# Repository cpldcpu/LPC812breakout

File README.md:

LPC812breakout
==============

Breakout Board for the NXP LPC812M101JPH20 microcontroller. Includes push buttons for reset and activating the serial bootloader. 
The board has an integrated 500mA 3.3V LDO to supply both the MCU and connected devices from the USB port. 

The four pins on the top side (5V,RX,TX,GND) can be used to connect a cheap USB to serial adapter (<$2 on ebay) and program the device via the internal bootloader using FlashMagic. Note that you have to cross RX and TX. RX from the serial port goes to TX and vice versa for TX.

 * FlashMagic can be downloaded [here](http://www.flashmagictool.com/).
 * Developer environemt and LPC800 datasheets by NXP can be found  [here](http://www.lpcware.com/content/device/lpc800).

The entire board with LPC812 is smaller than a DIP LPC1114. See below for size comparison.

Bonus: Eagle Library for all LPC800 parts

You can order PCB's here: [Shared design at OSH Park](http://oshpark.com/shared_projects/rQra0bCX) The price is $3.30 including shipping for three boards.

Status
======

 - 2013/09/17 Untested. Board ordered at OSH park
 - 2013/09/29 Designed revision 2
 - 2013/10/?? Version 2 board received, built and tested. Everything works as intended.
 
## Top side ##

## Bottom ##

## Size comparison of first version to LPC1114 ##

## On breadboard ##

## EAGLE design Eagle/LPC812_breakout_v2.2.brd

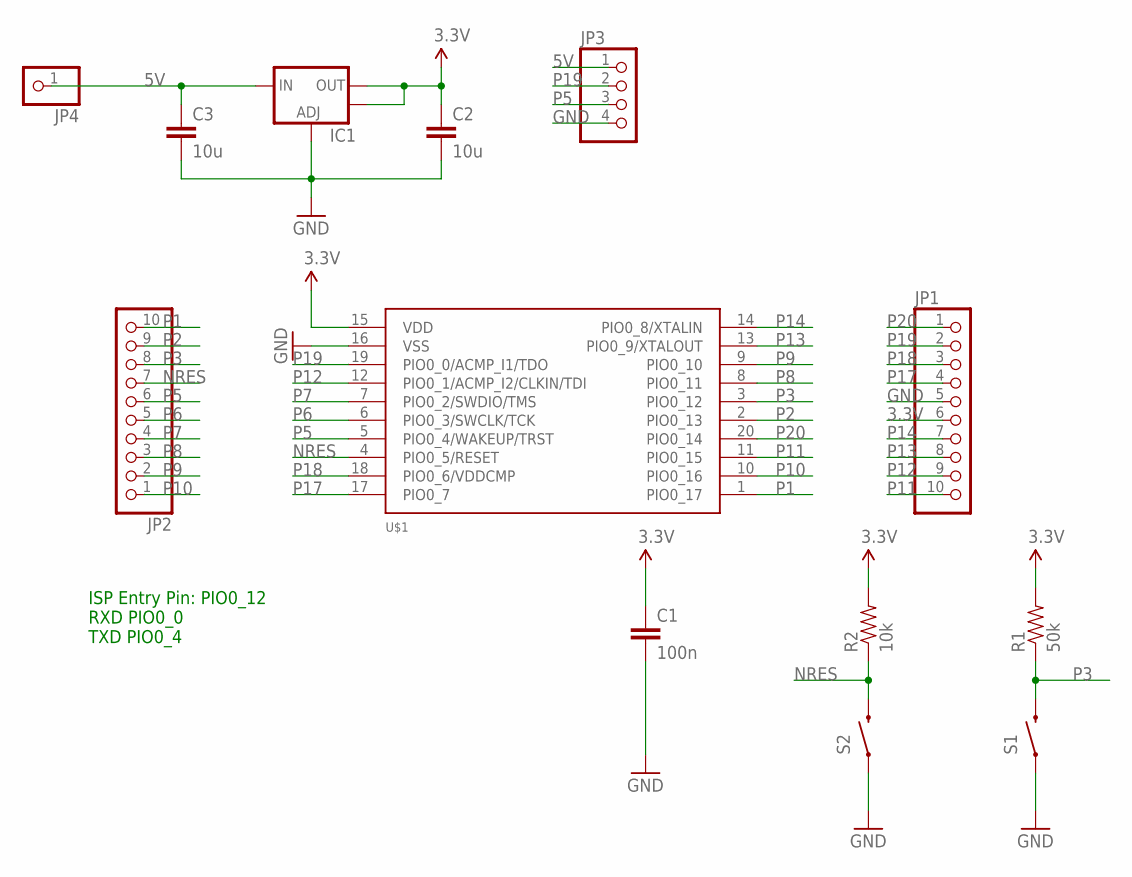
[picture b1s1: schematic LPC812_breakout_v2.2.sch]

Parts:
C1: 100n; 0805
C2, C3: 10u; 0805
IC1: V_REG_LM1117SOT223; SOT223
JP1, JP2: HEADER-1X10ROUND; 1X10_ROUND
JP3: HEADER-1X4ROUND; 1X04_ROUND
JP4: HEADER-1X1ROUND; 1X01_ROUND
R1: 50k; 0805
R2: 10k; 0805
S1, S2: SWITCH-MOMENTARY-2-SMD-1101NE; TACTILE-SWITCH-1101NE
U$1: LPC812M101JDH20; TSSOP20

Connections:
3.3V: C1.1, C2.1, IC1.2 (OUT), IC1.4 (OUT), JP1.6, R1.2, R2.2, U$1.15 (VDD)
5V: C3.1, IC1.3 (IN), JP3.1, JP4.1
GND: C1.2, C2.2, C3.2, IC1.1 (ADJ), JP1.5, JP3.4, S1.P$1 (1), S2.P$1 (1), U$1.16 (VSS)
NRES: JP2.7, R2.1, S2.P$2 (2), U$1.4 (PIO0_5/RESET)
P1: JP2.10, U$1.1 (PIO0_17)
P2: JP2.9, U$1.2 (PIO0_13)
P3: JP2.8, R1.1, S1.P$2 (2), U$1.3 (PIO0_12)
P5: JP2.6, JP3.3, U$1.5 (PIO0_4/WAKEUP/TRST)
P6: JP2.5, U$1.6 (PIO0_3/SWCLK/TCK)
P7: JP2.4, U$1.7 (PIO0_2/SWDIO/TMS)
P8: JP2.3, U$1.8 (PIO0_11)
P9: JP2.2, U$1.9 (PIO0_10)
P10: JP2.1, U$1.10 (PIO0_16)
P11: JP1.10, U$1.11 (PIO0_15)
P12: JP1.9, U$1.12 (PIO0_1/ACMP_I2/CLKIN/TDI)
P13: JP1.8, U$1.13 (PIO0_9/XTALOUT)
P14: JP1.7, U$1.14 (PIO0_8/XTALIN)
P17: JP1.4, U$1.17 (PIO0_7)
P18: JP1.3, U$1.18 (PIO0_6/VDDCMP)
P19: JP1.2, JP3.2, U$1.19 (PIO0_0/ACMP_I1/TDO)
P20: JP1.1, U$1.20 (PIO0_14)

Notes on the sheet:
ISP Entry Pin: PIO0_12 RXD PIO0_0 TXD PIO0_4

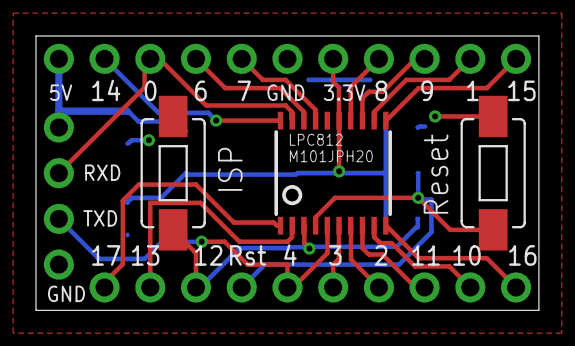
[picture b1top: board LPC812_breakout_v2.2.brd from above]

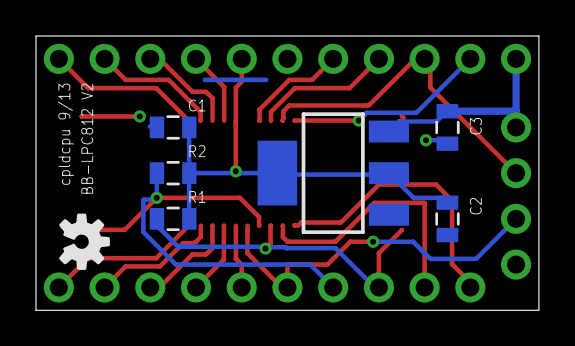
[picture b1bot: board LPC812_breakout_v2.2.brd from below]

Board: 2 copper layers, 27.9 x 15.2 mm, 14 parts (7 on the bottom side), 21 nets.

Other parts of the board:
U$2: OSHW-LOGO-S

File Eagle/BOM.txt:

# Part  Type            Value                         Package               Pins
1 C1    Capacitor       100n                          805                   2
2 C2    Cap. MLCC 10V   10u                           805                   2
3 C3    Cap. MLCC 10V   10u                           805                   2
4 IC1   LDO             AMS1117-3.3                   SOT223                3
5 R1    Resistor        50k                           805                   2
6 R2    Resistor        10k                           805                   2
7 S1    Pushbutton      SWITCH-MOMENTARY-2-SMD-1101NE TACTILE-SWITCH-1101NE 2
8 S2    Pushbutton      SWITCH-MOMENTARY-2-SMD-1101NE TACTILE-SWITCH-1101NE 2
9 IC2   Controller      NXP LPC812M101JDH20           TSSOP20               20

In addition:

10 	Pin Header	10x1
11 	Pin Header	11x1
12 	Pin Header	4x1

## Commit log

2013-09-29 Update README.md
    rev2
2013-09-29 Revision 2
    Changes:
    - 10 mil traces, no 90° bends, ground plane where possible.
    - Font size for pin labelling increased.
    - Removed SWD port to reduce complexity and size. If needed, the board
    can be accessed at the broken out pins.
    - Included 3.3V regulator, since the driving ability of those includede
2013-09-29 Revision 2.2 - Broke out 5V pin
2013-11-18 photos of second version
2013-11-18 move images
2013-11-19 images
2013-11-20 added schematics
2014-01-14 clarified OSH Park link
2014-01-19 added schematics as pdf
2014-01-30 Added BOM

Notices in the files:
parts and their libraries:
microbuilder: This work is placed in the public domain, and may be freely used for commercial and non-commercial work with the following conditions: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
SparkFun-Capacitors: Licensing: CC v3.0 Share-Alike You are welcome to use this library for commercial purposes.
